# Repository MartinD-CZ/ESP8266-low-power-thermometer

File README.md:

# ESP8266 ultra low power thermometer
*see the article [here](http://embedblog.eu/?p=36)*

## Specs
1. Arduino-compatible
2. lasts more than 2 years on a pair of AA batteries
3. measures temperature and pressure (BMP280) OR temperature, humidity and pressure (BME280)
4. transmits data regularly to Blynk (or other platform, if you program it for it)
5. can be programmed with just a simple USB-Serial converter

## Required libraries
* [ESP8266 core](https://github.com/esp8266/Arduino)
* [Blynk library](https://github.com/blynkkk/blynk-library)
* [BMP280 library](https://github.com/mahfuz195/BMP280-Arduino-Library)

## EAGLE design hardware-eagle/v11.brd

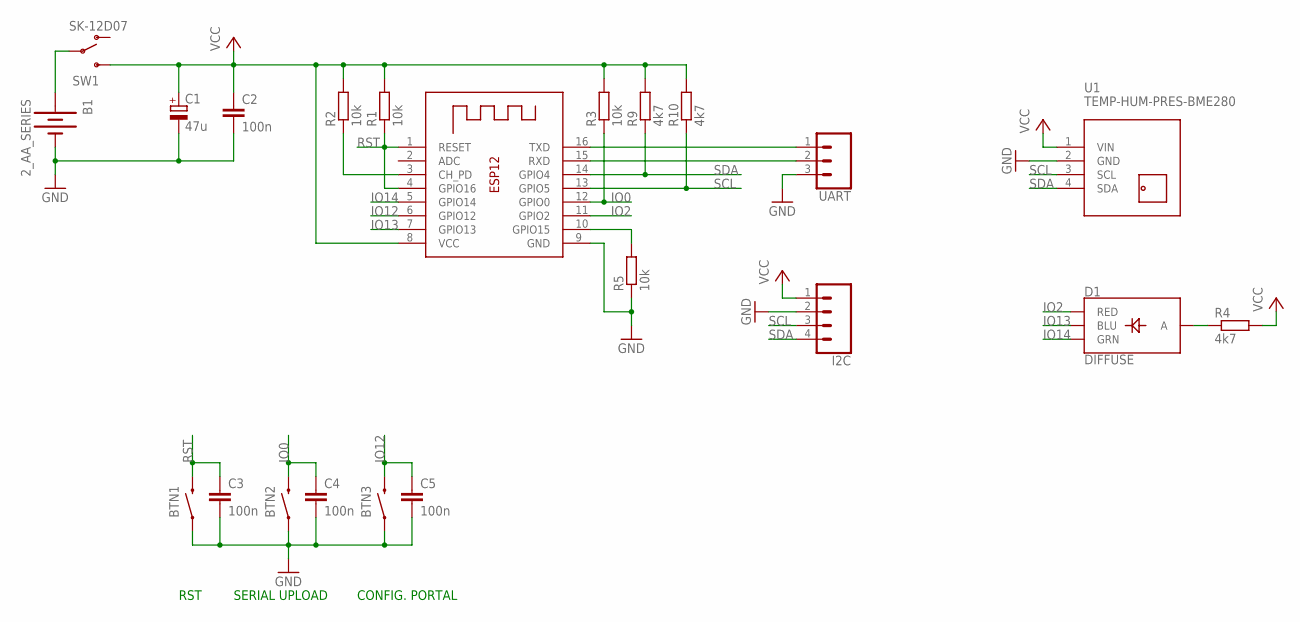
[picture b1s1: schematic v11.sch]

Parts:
B1: 2_AA_SERIES; AA_HOLDER_BH-321-1P
BTN1, BTN2, BTN3: MOMENTARY-SWITCH-SPST-PTH-6.0MM; TACTILE_SWITCH_PTH_6.0MM
C1: 47u; SMC_B
C2, C3, C4, C5: 100n; C1206
D1: DIFFUSE; LED-RGB-THRU
I2C: CONN_04; 1X04
R1, R2, R3, R5: 10k; R1206
R4, R9, R10: 4k7; R1206
SW1: SK-12D07; SK12SWITCH
U1: TEMP-HUM-PRES-BME280
UART: 455-1750-1-ND; 1X03
X1: ESP-12

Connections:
GND: B1.NEG (-), BTN1.1, BTN2.1, BTN3.1, C1.-, C2.2, C3.2, C4.2, C5.2, I2C.2, R5.1, U1.2 (GND), UART.3, X1.9 (GND)
IO0: BTN2.3 (2), C4.1, R3.1, X1.12 (GPIO0)
IO2: D1.1 (RED), X1.11 (GPIO2)
IO12: BTN3.3 (2), C5.1, X1.6 (GPIO12)
IO13: D1.4 (BLU), X1.7 (GPIO13)
IO14: D1.3 (GRN), X1.5 (GPIO14)
unnamed: D1.2 (A), R4.1
unnamed: R2.1, X1.3 (CH_PD)
unnamed: R5.2, X1.10 (GPIO15)
unnamed: B1.POS (+), SW1.P2
RST: BTN1.3 (2), C3.1, R1.1, X1.1 (RESET), X1.4 (GPIO16)
RX: UART.2, X1.15 (RXD)
SCL: I2C.3, R10.1, U1.3 (SCL), X1.13 (GPIO5)
SDA: I2C.4, R9.1, U1.4 (SDA), X1.14 (GPIO4)
TX: UART.1, X1.16 (TXD)
VCC: C1.+, C2.1, I2C.1, R1.2, R2.2, R3.2, R4.2, R9.2, R10.2, SW1.IN (S), U1.1 (VIN), X1.8 (VCC)

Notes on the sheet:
RST
SERIAL UPLOAD
CONFIG. PORTAL

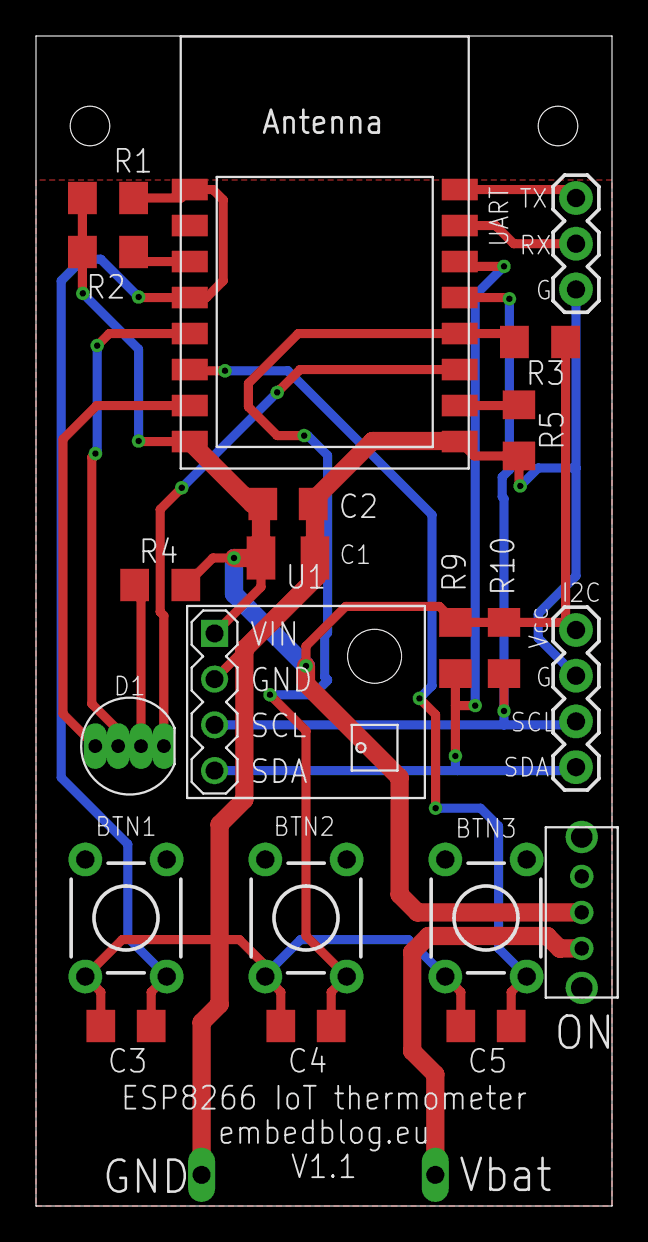
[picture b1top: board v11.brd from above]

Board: 2 copper layers, 32.0 x 65.0 mm, 22 parts (1 on the bottom side), 16 nets.

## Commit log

2019-04-27 initial release

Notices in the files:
parts and their libraries:
SparkFun-Switches: Licensing: Creative Commons ShareAlike 4.0 International - https://creativecommons.org/licenses/by-sa/4.0
diy-modules: Released under the Creative Commons Attribution 4.0 International License: http://creativecommons.org/licenses/by/4.0
